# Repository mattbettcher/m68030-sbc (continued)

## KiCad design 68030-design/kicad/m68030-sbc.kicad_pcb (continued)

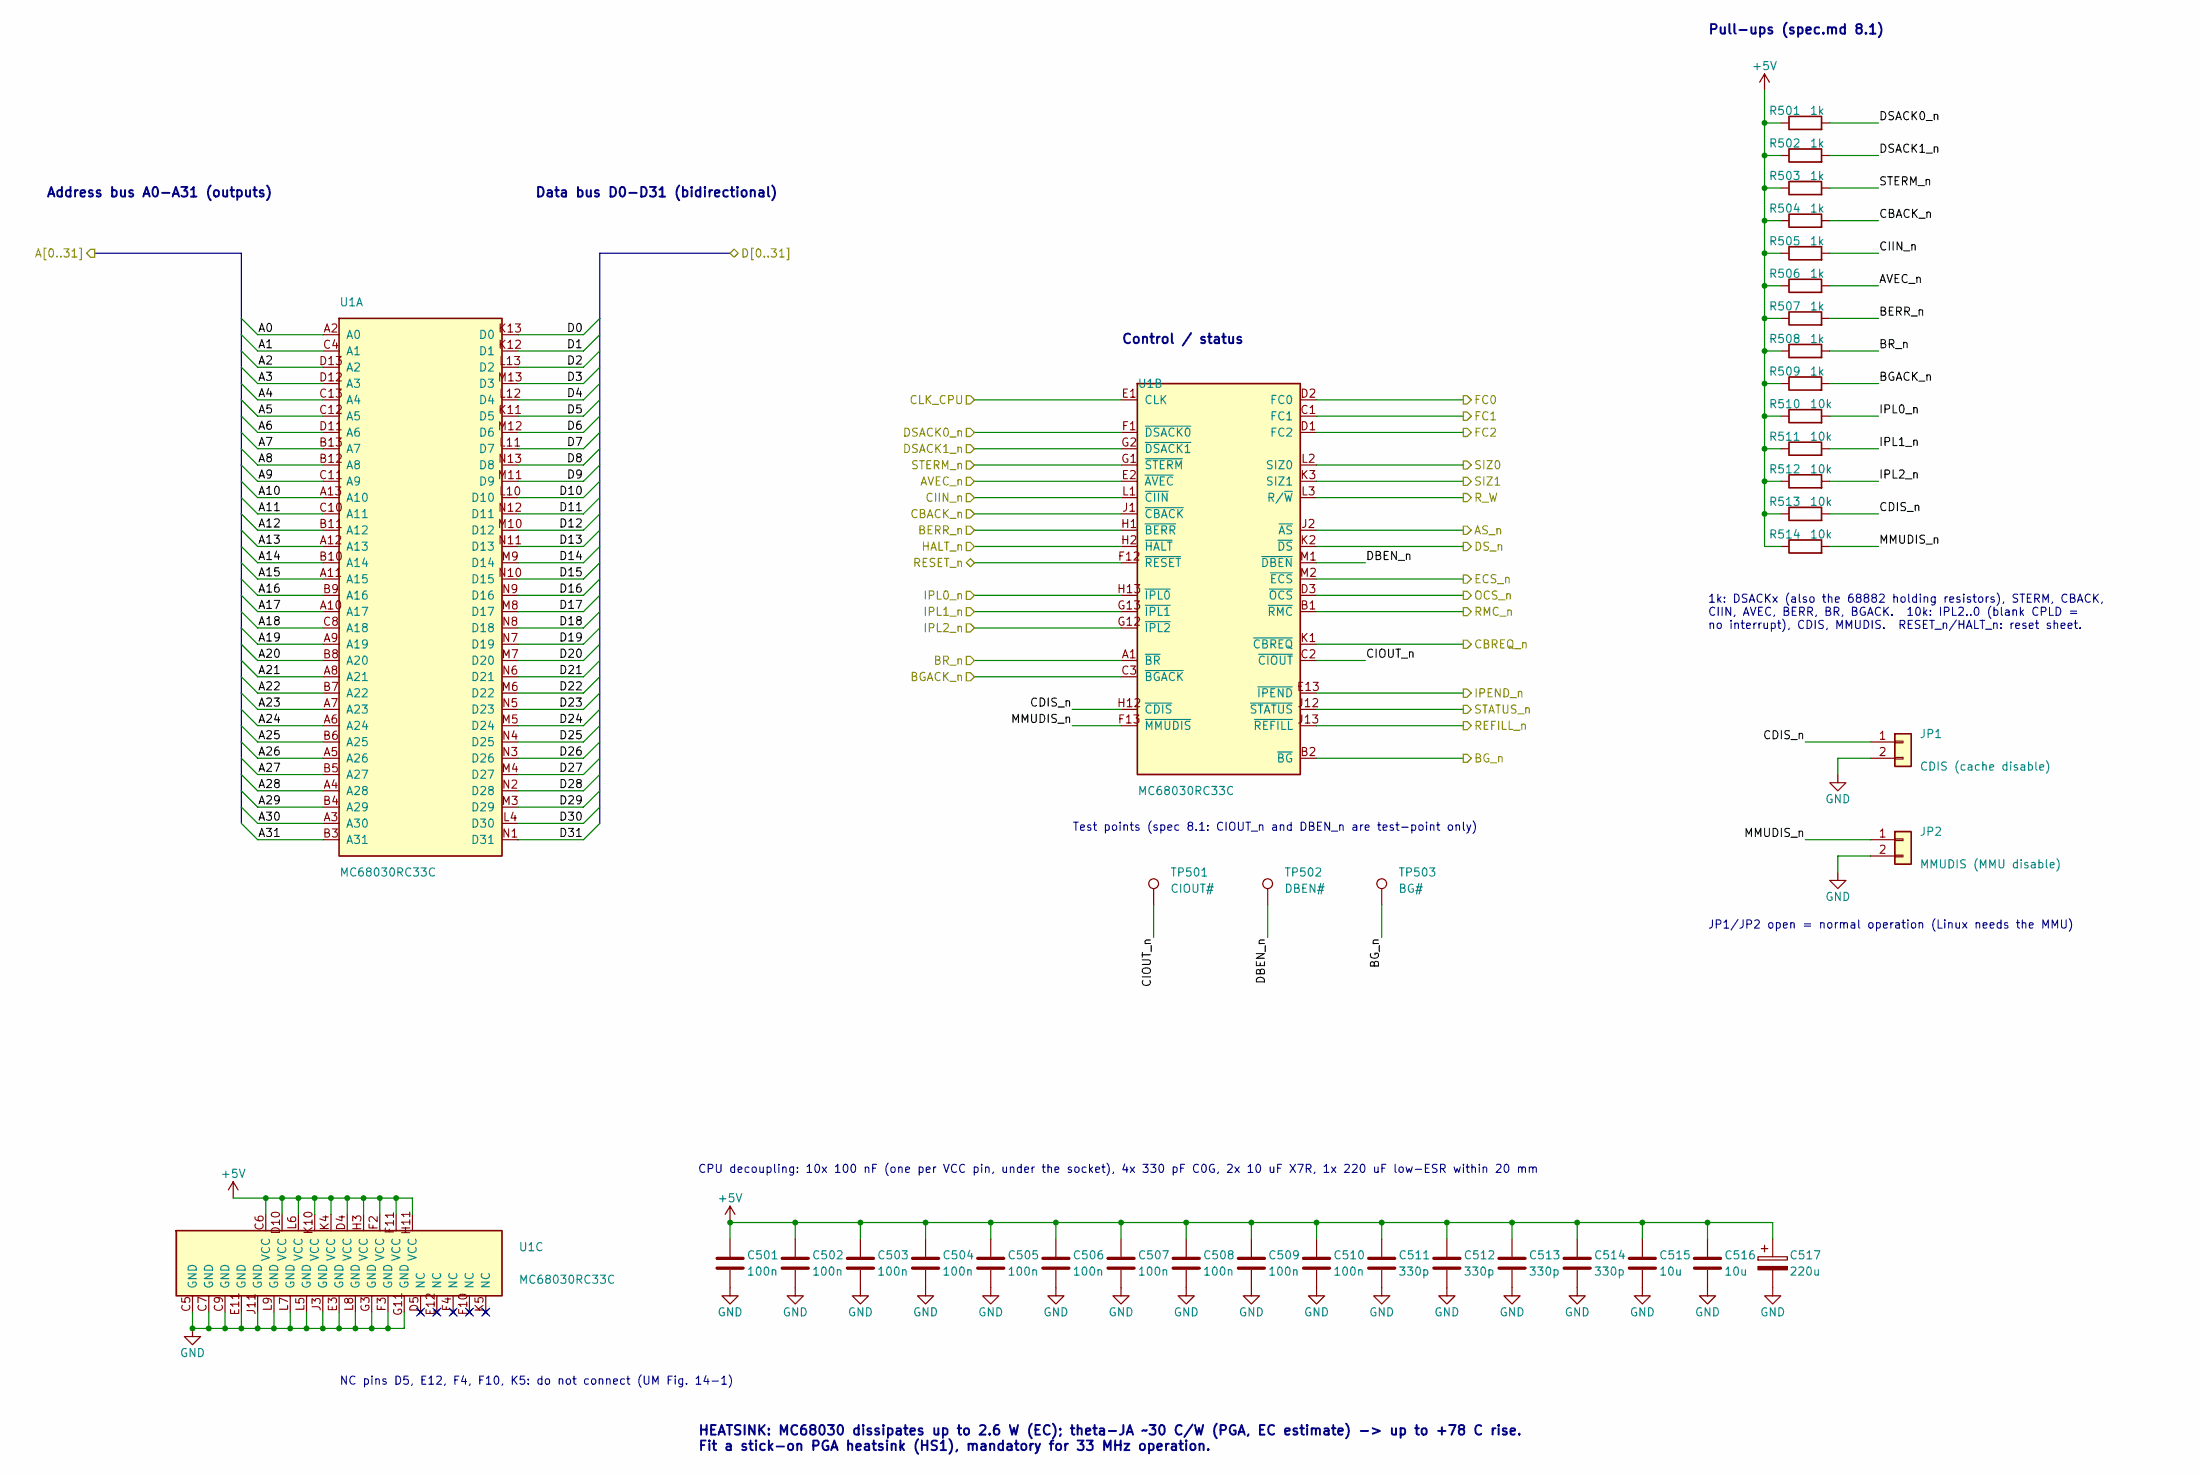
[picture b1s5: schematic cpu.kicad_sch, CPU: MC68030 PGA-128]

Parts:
C501, C502, C503, C504, C505, C506, C507, C508, C509, C510: 100n; C_0805_2012Metric
C511, C512, C513, C514: 330p; C_0603_1608Metric
C515, C516: 10u; C_1206_3216Metric
C517: 220u; CP_Radial_D8.0mm_P3.50mm
JP1: CDIS (cache disable); PinHeader_1x02_P2.54mm_Vertical
JP2: MMUDIS (MMU disable); PinHeader_1x02_P2.54mm_Vertical
R501, R502, R503, R504, R505, R506, R507, R508, R509: 1k; R_0603_1608Metric
R510, R511, R512, R513, R514: 10k; R_0603_1608Metric
TP501: CIOUT#; TestPoint_Pad_D1.5mm
TP502: DBEN#; TestPoint_Pad_D1.5mm
TP503: BG#; TestPoint_Pad_D1.5mm
U1: MC68030RC33C; PGA128_13x13_MC68030; MPN MC68030RC33C

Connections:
+5V: C501.1, C502.1, C503.1, C504.1, C505.1, C506.1, C507.1, C508.1, C509.1, C510.1, C511.1, C512.1, C513.1, C514.1, C515.1, C516.1, C517.1, R501.1, R502.1, R503.1, R504.1, R505.1, R506.1, R507.1, R508.1, R509.1, R510.1, R511.1, R512.1, R513.1, R514.1, U1.C6 (VCC), U1.D4 (VCC), U1.D10 (VCC), U1.F2 (VCC), U1.F11 (VCC), U1.H3 (VCC), U1.H11 (VCC), U1.K4 (VCC), U1.K10 (VCC), U1.L6 (VCC); also elsewhere on the board
/A0: U1.A2 (A0); also elsewhere on the board
/A1: U1.C4 (A1); also elsewhere on the board
/A2: U1.D13 (A2); also elsewhere on the board
/A3: U1.D12 (A3); also elsewhere on the board
/A4: U1.C13 (A4); also elsewhere on the board
/A5: U1.C12 (A5); also elsewhere on the board
/A6: U1.D11 (A6); also elsewhere on the board
/A7: U1.B13 (A7); also elsewhere on the board
/A8: U1.B12 (A8); also elsewhere on the board
/A9: U1.C11 (A9); also elsewhere on the board
/A10: U1.A13 (A10); also elsewhere on the board
/A11: U1.C10 (A11); also elsewhere on the board
/A12: U1.B11 (A12); also elsewhere on the board
/A13: U1.A12 (A13); also elsewhere on the board
/A14: U1.B10 (A14); also elsewhere on the board
/A15: U1.A11 (A15); also elsewhere on the board
/A16: U1.B9 (A16); also elsewhere on the board
/A17: U1.A10 (A17); also elsewhere on the board
/A18: U1.C8 (A18); also elsewhere on the board
/A19: U1.A9 (A19); also elsewhere on the board
/A20: U1.B8 (A20); also elsewhere on the board
/A21: U1.A8 (A21); also elsewhere on the board
/A22: U1.B7 (A22); also elsewhere on the board
/A23: U1.A7 (A23); also elsewhere on the board
/A24: U1.A6 (A24); also elsewhere on the board
/A25: U1.B6 (A25); also elsewhere on the board
/A26: U1.A5 (A26); also elsewhere on the board
/A27: U1.B5 (A27); also elsewhere on the board
/A28: U1.A4 (A28); also elsewhere on the board
/A29: U1.B4 (A29); also elsewhere on the board
/A30: U1.A3 (A30); also elsewhere on the board
/A31: U1.B3 (A31); also elsewhere on the board
/AS_n: U1.J2 (~AS); also elsewhere on the board
/AVEC_n: R506.2, U1.E2 (~AVEC); also elsewhere on the board
/BERR_n: R507.2, U1.H1 (~BERR); also elsewhere on the board
/BGACK_n: R509.2, U1.C3 (~BGACK); also elsewhere on the board
/BG_n: TP503.1, U1.B2 (~BG); also elsewhere on the board
/BR_n: R508.2, U1.A1 (~BR); also elsewhere on the board
/CBACK_n: R504.2, U1.J1 (~CBACK); also elsewhere on the board
/CBREQ_n: U1.K1 (~CBREQ); also elsewhere on the board
/CIIN_n: R505.2, U1.L1 (~CIIN); also elsewhere on the board
/CLK_CPU: U1.E1 (CLK); also elsewhere on the board
/D0: U1.K13 (D0); also elsewhere on the board
/D1: U1.K12 (D1); also elsewhere on the board
/D2: U1.L13 (D2); also elsewhere on the board
/D3: U1.M13 (D3); also elsewhere on the board
/D4: U1.L12 (D4); also elsewhere on the board
/D5: U1.K11 (D5); also elsewhere on the board
/D6: U1.M12 (D6); also elsewhere on the board
/D7: U1.L11 (D7); also elsewhere on the board
/D8: U1.N13 (D8); also elsewhere on the board
/D9: U1.M11 (D9); also elsewhere on the board
/D10: U1.L10 (D10); also elsewhere on the board
/D11: U1.N12 (D11); also elsewhere on the board
/D12: U1.M10 (D12); also elsewhere on the board
/D13: U1.N11 (D13); also elsewhere on the board
/D14: U1.M9 (D14); also elsewhere on the board
/D15: U1.N10 (D15); also elsewhere on the board
/D16: U1.N9 (D16); also elsewhere on the board
/D17: U1.M8 (D17); also elsewhere on the board
/D18: U1.N8 (D18); also elsewhere on the board
/D19: U1.N7 (D19); also elsewhere on the board
/D20: U1.M7 (D20); also elsewhere on the board
/D21: U1.N6 (D21); also elsewhere on the board
/D22: U1.M6 (D22); also elsewhere on the board
/D23: U1.N5 (D23); also elsewhere on the board
/D24: U1.M5 (D24); also elsewhere on the board
/D25: U1.N4 (D25); also elsewhere on the board
/D26: U1.N3 (D26); also elsewhere on the board
/D27: U1.M4 (D27); also elsewhere on the board
/D28: U1.N2 (D28); also elsewhere on the board
/D29: U1.M3 (D29); also elsewhere on the board
/D30: U1.L4 (D30); also elsewhere on the board
/D31: U1.N1 (D31); also elsewhere on the board
/DSACK0_n: R501.2, U1.F1 (~DSACK0); also elsewhere on the board
/DSACK1_n: R502.2, U1.G2 (~DSACK1); also elsewhere on the board
/DS_n: U1.K2 (~DS); also elsewhere on the board
/ECS_n: U1.M2 (~ECS); also elsewhere on the board
/FC0: U1.D2 (FC0); also elsewhere on the board
/FC1: U1.C1 (FC1); also elsewhere on the board
/FC2: U1.D1 (FC2); also elsewhere on the board
/HALT_n: U1.H2 (~HALT); also elsewhere on the board
/IPEND_n: U1.E13 (~IPEND); also elsewhere on the board
/IPL0_n: R510.2, U1.H13 (~IPL0); also elsewhere on the board
/IPL1_n: R511.2, U1.G13 (~IPL1); also elsewhere on the board
/IPL2_n: R512.2, U1.G12 (~IPL2); also elsewhere on the board
/OCS_n: U1.D3 (~OCS); also elsewhere on the board
/REFILL_n: U1.J13 (~REFILL); also elsewhere on the board
/RESET_n: U1.F12 (~RESET); also elsewhere on the board
/RMC_n: U1.B1 (~RMC); also elsewhere on the board
/R_W: U1.L3 (R/~W); also elsewhere on the board
/SIZ0: U1.L2 (SIZ0); also elsewhere on the board
/SIZ1: U1.K3 (SIZ1); also elsewhere on the board
/STATUS_n: U1.J12 (~STATUS); also elsewhere on the board
/STERM_n: R503.2, U1.G1 (~STERM); also elsewhere on the board
/cpu/CDIS_n: JP1.1, R513.2, U1.H12 (~CDIS)
/cpu/CIOUT_n: TP501.1, U1.C2 (~CIOUT)
/cpu/DBEN_n: TP502.1, U1.M1 (~DBEN)
/cpu/MMUDIS_n: JP2.1, R514.2, U1.F13 (~MMUDIS)
GND: C501.2, C502.2, C503.2, C504.2, C505.2, C506.2, C507.2, C508.2, C509.2, C510.2, C511.2, C512.2, C513.2, C514.2, C515.2, C516.2, C517.2, JP1.2, JP2.2, U1.C5 (GND), U1.C7 (GND), U1.C9 (GND), U1.E3 (GND), U1.E11 (GND), U1.F3 (GND), U1.G3 (GND), U1.G11 (GND), U1.J3 (GND), U1.J11 (GND), U1.L5 (GND), U1.L7 (GND), U1.L8 (GND), U1.L9 (GND); also elsewhere on the board

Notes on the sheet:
Address bus A0-A31 (outputs)
Data bus D0-D31 (bidirectional)
Control / status
Test points (spec 8.1: CIOUT_n and DBEN_n are test-point only)
Pull-ups (spec.md 8.1)
1k: DSACKx (also the 68882 holding resistors), STERM, CBACK, CIIN, AVEC, BERR, BR, BGACK. 10k: IPL2..0 (blank CPLD = no interrupt), CDIS, MMUDIS. RESET_n/HALT_n: reset sheet.
JP1/JP2 open = normal operation (Linux needs the MMU)
NC pins D5, E12, F4, F10, K5: do not connect (UM Fig. 14-1)
CPU decoupling: 10x 100 nF (one per VCC pin, under the socket), 4x 330 pF C0G, 2x 10 uF X7R, 1x 220 uF low-ESR within 20 mm
HEATSINK: MC68030 dissipates up to 2.6 W (EC); theta-JA ~30 C/W (PGA, EC estimate) -> up to +78 C rise. Fit a stick-on PGA heatsink (HS1), mandatory for 33 MHz operation.

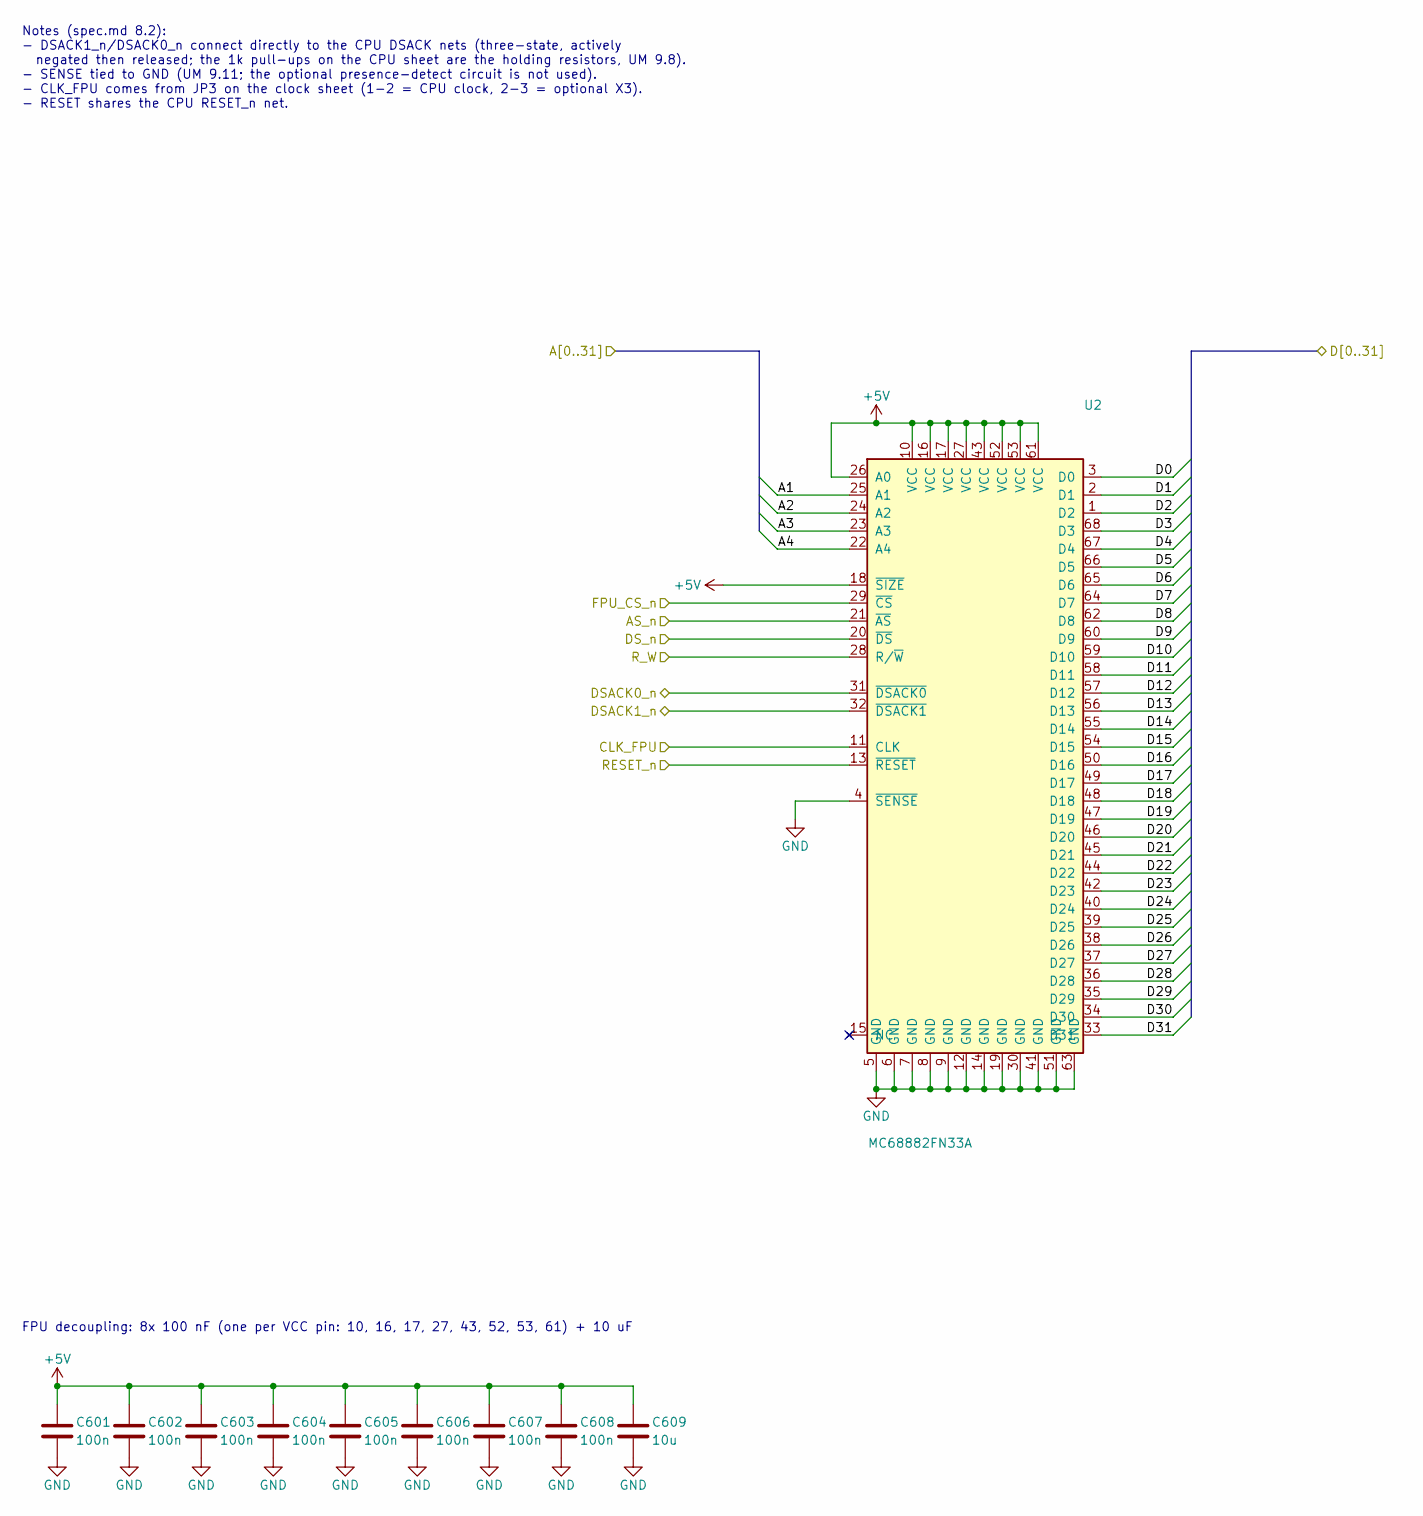
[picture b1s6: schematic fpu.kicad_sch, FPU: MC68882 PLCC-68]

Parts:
C601, C602, C603, C604, C605, C606, C607, C608: 100n; C_0805_2012Metric
C609: 10u; C_1206_3216Metric
U2: MC68882FN33A; PLCC-68_THT-Socket; MPN MC68882FN33A (or FN25A)

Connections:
+5V: C601.1, C602.1, C603.1, C604.1, C605.1, C606.1, C607.1, C608.1, C609.1, U2.10 (VCC), U2.16 (VCC), U2.17 (VCC), U2.18 (~SIZE), U2.26 (A0), U2.27 (VCC), U2.43 (VCC), U2.52 (VCC), U2.53 (VCC), U2.61 (VCC); also elsewhere on the board
/A1: U2.25 (A1); also elsewhere on the board
/A2: U2.24 (A2); also elsewhere on the board
/A3: U2.23 (A3); also elsewhere on the board
/A4: U2.22 (A4); also elsewhere on the board
/AS_n: U2.21 (~AS); also elsewhere on the board
/CLK_FPU: U2.11 (CLK); also elsewhere on the board
/D0: U2.3 (D0); also elsewhere on the board
/D1: U2.2 (D1); also elsewhere on the board
/D2: U2.1 (D2); also elsewhere on the board
/D3: U2.68 (D3); also elsewhere on the board
/D4: U2.67 (D4); also elsewhere on the board
/D5: U2.66 (D5); also elsewhere on the board
/D6: U2.65 (D6); also elsewhere on the board
/D7: U2.64 (D7); also elsewhere on the board
/D8: U2.62 (D8); also elsewhere on the board
/D9: U2.60 (D9); also elsewhere on the board
/D10: U2.59 (D10); also elsewhere on the board
/D11: U2.58 (D11); also elsewhere on the board
/D12: U2.57 (D12); also elsewhere on the board
/D13: U2.56 (D13); also elsewhere on the board
/D14: U2.55 (D14); also elsewhere on the board
/D15: U2.54 (D15); also elsewhere on the board
/D16: U2.50 (D16); also elsewhere on the board
/D17: U2.49 (D17); also elsewhere on the board
/D18: U2.48 (D18); also elsewhere on the board
/D19: U2.47 (D19); also elsewhere on the board
/D20: U2.46 (D20); also elsewhere on the board
/D21: U2.45 (D21); also elsewhere on the board
/D22: U2.44 (D22); also elsewhere on the board
/D23: U2.42 (D23); also elsewhere on the board
/D24: U2.40 (D24); also elsewhere on the board
/D25: U2.39 (D25); also elsewhere on the board
/D26: U2.38 (D26); also elsewhere on the board
/D27: U2.37 (D27); also elsewhere on the board
/D28: U2.36 (D28); also elsewhere on the board
/D29: U2.35 (D29); also elsewhere on the board
/D30: U2.34 (D30); also elsewhere on the board
/D31: U2.33 (D31); also elsewhere on the board
/DSACK0_n: U2.31 (~DSACK0); also elsewhere on the board
/DSACK1_n: U2.32 (~DSACK1); also elsewhere on the board
/DS_n: U2.20 (~DS); also elsewhere on the board
/FPU_CS_n: U2.29 (~CS); also elsewhere on the board
/RESET_n: U2.13 (~RESET); also elsewhere on the board
/R_W: U2.28 (R/~W); also elsewhere on the board
GND: C601.2, C602.2, C603.2, C604.2, C605.2, C606.2, C607.2, C608.2, C609.2, U2.4 (~SENSE), U2.5 (GND), U2.6 (GND), U2.7 (GND), U2.8 (GND), U2.9 (GND), U2.12 (GND), U2.14 (GND), U2.19 (GND), U2.30 (GND), U2.41 (GND), U2.51 (GND), U2.63 (GND); also elsewhere on the board

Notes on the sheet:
FPU decoupling: 8x 100 nF (one per VCC pin: 10, 16, 17, 27, 43, 52, 53, 61) + 10 uF
Notes (spec.md 8.2): - DSACK1_n/DSACK0_n connect directly to the CPU DSACK nets (three-state, actively negated then released; the 1k pull-ups on the CPU sheet are the holding resistors, UM 9.8). - SENSE tied to GND (UM 9.11; the optional presence-detect circuit is not used). - CLK_FPU comes from JP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

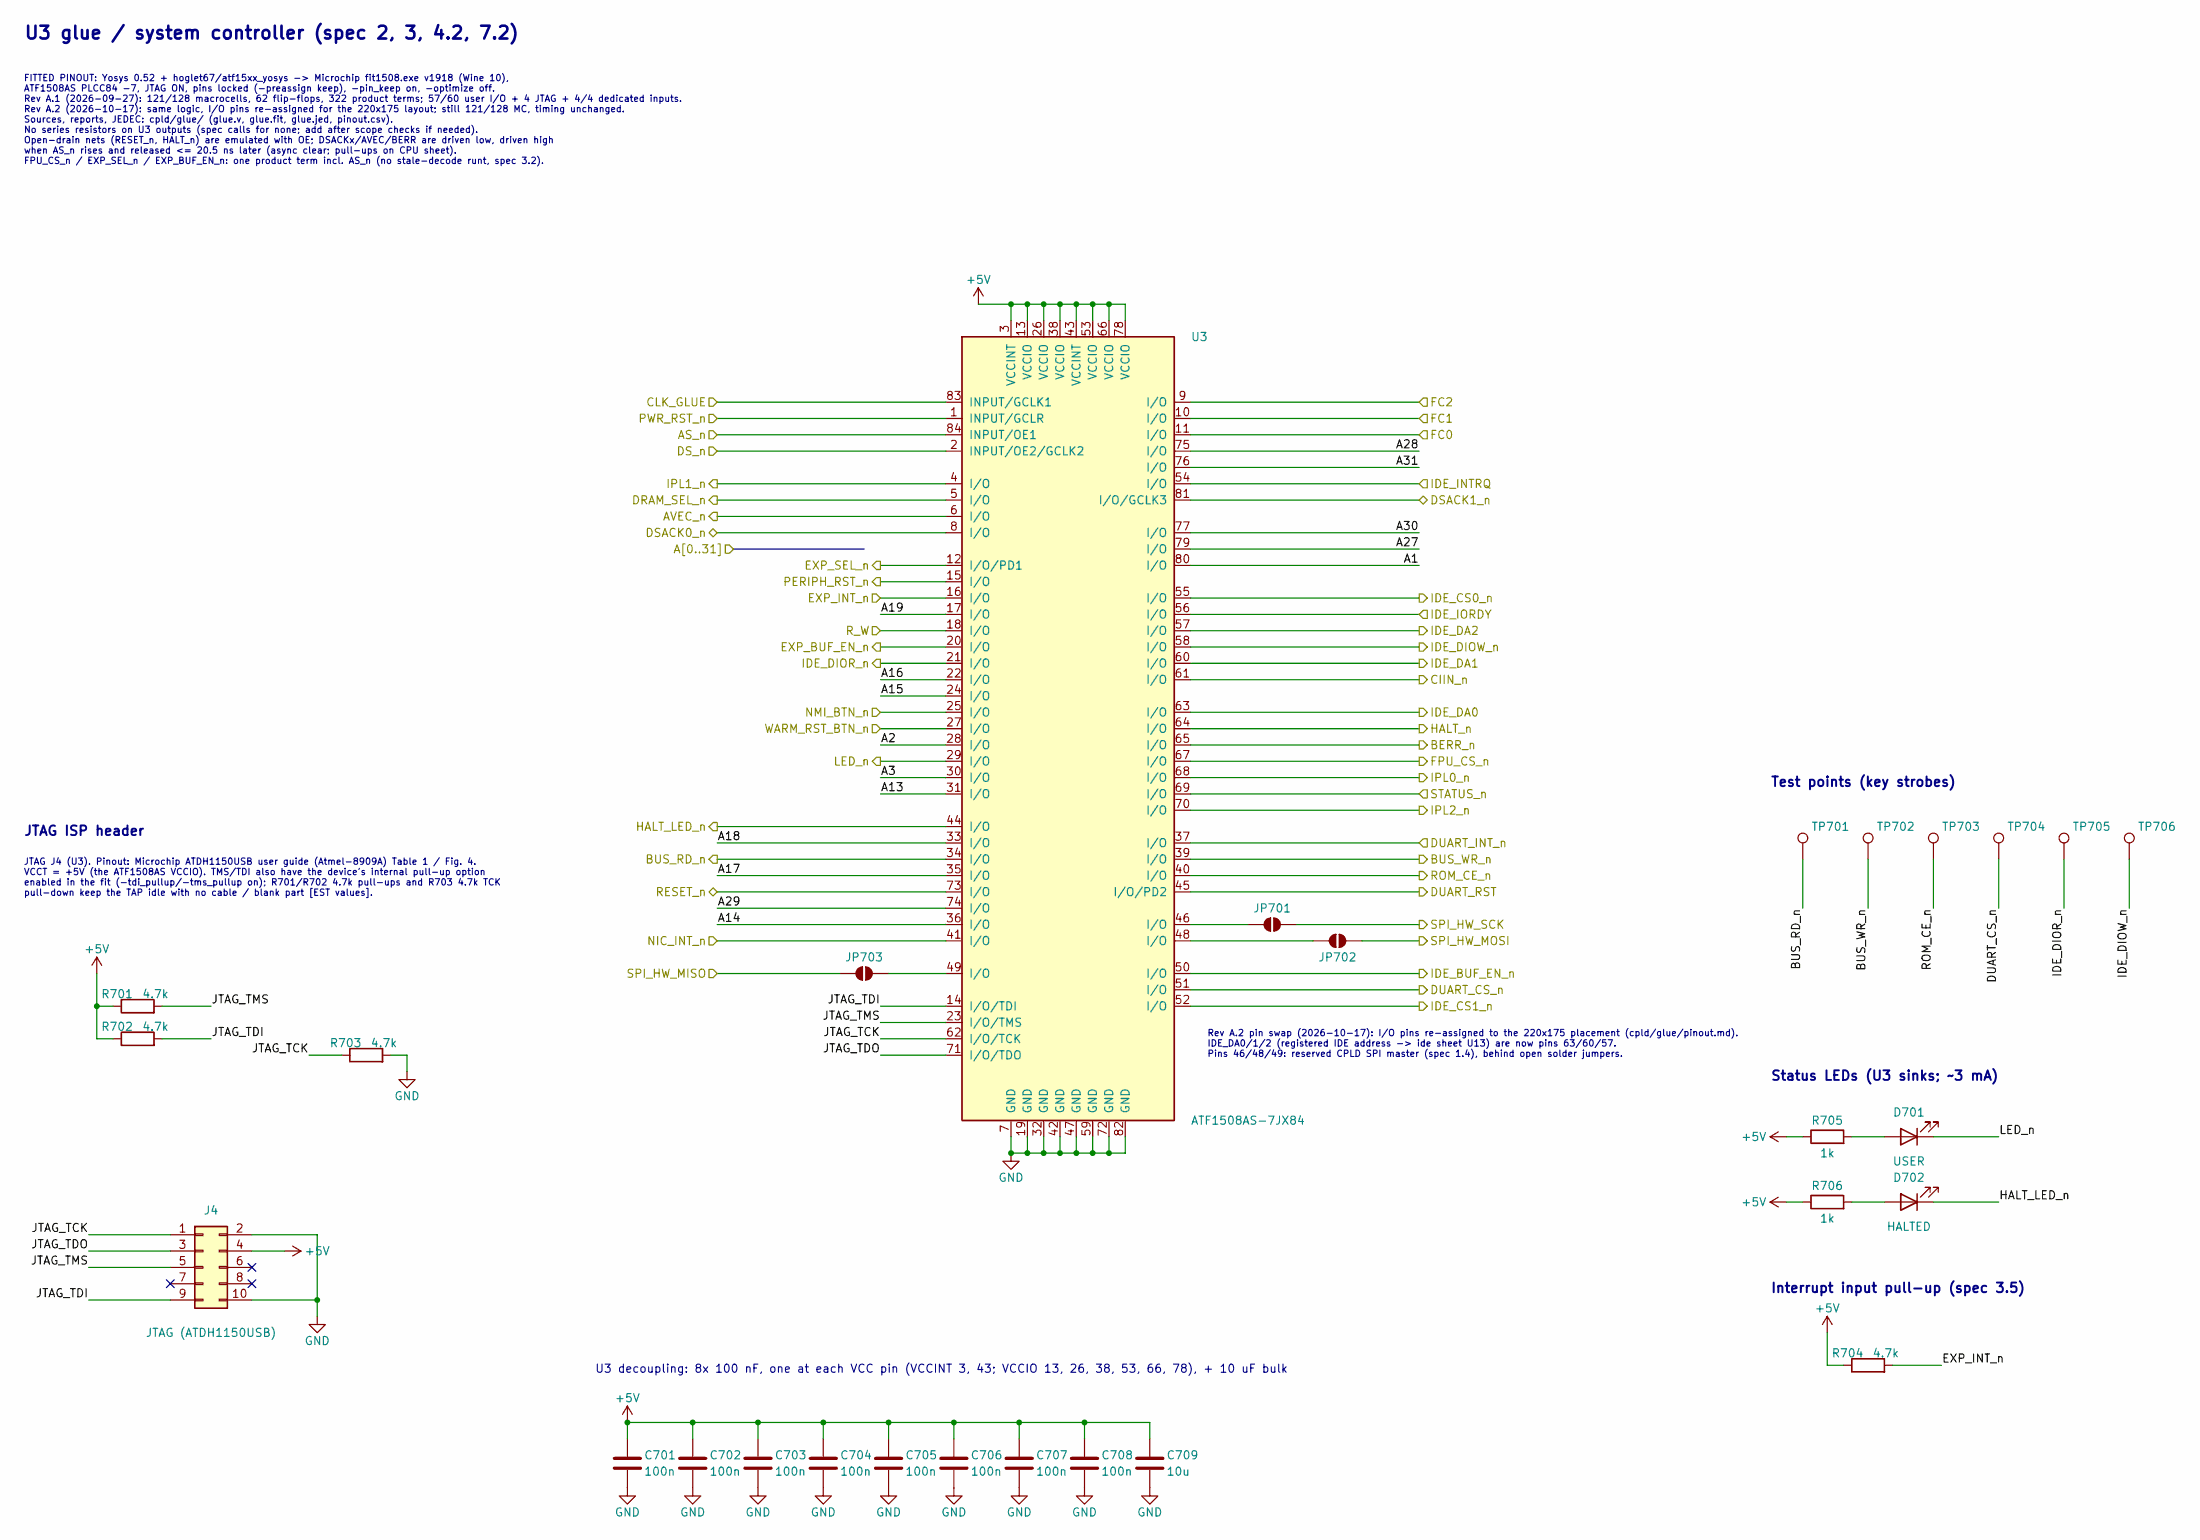
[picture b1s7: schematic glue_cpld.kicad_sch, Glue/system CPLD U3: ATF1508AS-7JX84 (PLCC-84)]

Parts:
C701, C702, C703, C704, C705, C706, C707, C708: 100n; C_0805_2012Metric
C709: 10u; C_1206_3216Metric
D701: USER; LED_0805_2012Metric
D702: HALTED; LED_0805_2012Metric
J4: JTAG (ATDH1150USB); IDC-Header_2x05_P2.54mm_Vertical
JP701, JP702, JP703: open; SolderJumper-2_P1.3mm_Open_RoundedPad1.0x1.5mm
R701, R702, R703, R704: 4.7k; R_0603_1608Metric
R705, R706: 1k; R_0603_1608Metric
TP701: BUS_RD#; TestPoint_Pad_D1.5mm
TP702: BUS_WR#; TestPoint_Pad_D1.5mm
TP703: ROM_CE#; TestPoint_Pad_D1.5mm
TP704: DUART_CS#; TestPoint_Pad_D1.5mm
TP705: IDE_DIOR#; TestPoint_Pad_D1.5mm
TP706: IDE_DIOW#; TestPoint_Pad_D1.5mm
U3: ATF1508AS-7JX84; PLCC-84_THT-Socket; MPN ATF1508AS-7JX84

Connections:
+5V: C701.1, C702.1, C703.1, C704.1, C705.1, C706.1, C707.1, C708.1, C709.1, J4.4, R701.1, R702.1, R704.1, R705.1, R706.1, U3.3 (VCCINT), U3.13 (VCCIO), U3.26 (VCCIO), U3.38 (VCCIO), U3.43 (VCCINT), U3.53 (VCCIO), U3.66 (VCCIO), U3.78 (VCCIO); also elsewhere on the board
/A1: U3.80 (I/O); also elsewhere on the board
/A2: U3.28 (I/O); also elsewhere on the board
/A3: U3.30 (I/O); also elsewhere on the board
/A13: U3.31 (I/O); also elsewhere on the board
/A14: U3.36 (I/O); also elsewhere on the board
/A15: U3.24 (I/O); also elsewhere on the board
/A16: U3.22 (I/O); also elsewhere on the board
/A17: U3.35 (I/O); also elsewhere on the board
/A18: U3.33 (I/O); also elsewhere on the board
/A19: U3.17 (I/O); also elsewhere on the board
/A27: U3.79 (I/O); also elsewhere on the board
/A28: U3.75 (I/O); also elsewhere on the board
/A29: U3.74 (I/O); also elsewhere on the board
/A30: U3.77 (I/O); also elsewhere on the board
/A31: U3.76 (I/O); also elsewhere on the board
/AS_n: U3.84 (INPUT/OE1); also elsewhere on the board
/AVEC_n: U3.6 (I/O); also elsewhere on the board
/BERR_n: U3.65 (I/O); also elsewhere on the board
/BUS_RD_n: TP701.1, U3.34 (I/O); also elsewhere on the board
/BUS_WR_n: TP702.1, U3.39 (I/O); also elsewhere on the board
/CIIN_n: U3.61 (I/O); also elsewhere on the board
/CLK_GLUE: U3.83 (INPUT/GCLK1); also elsewhere on the board
/DRAM_SEL_n: U3.5 (I/O); also elsewhere on the board
/DSACK0_n: U3.8 (I/O); also elsewhere on the board
/DSACK1_n: U3.81 (I/O/GCLK3); also elsewhere on the board
/DS_n: U3.2 (INPUT/OE2/GCLK2); also elsewhere on the board
/DUART_CS_n: TP704.1, U3.51 (I/O); also elsewhere on the board
/DUART_INT_n: U3.37 (I/O); also elsewhere on the board
/DUART_RST: U3.45 (I/O/PD2); also elsewhere on the board
/EXP_BUF_EN_n: U3.20 (I/O); also elsewhere on the board
/EXP_INT_n: R704.2, U3.16 (I/O); also elsewhere on the board
/EXP_SEL_n: U3.12 (I/O/PD1); also elsewhere on the board
/FC0: U3.11 (I/O); also elsewhere on the board
/FC1: U3.10 (I/O); also elsewhere on the board
/FC2: U3.9 (I/O); also elsewhere on the board
/FPU_CS_n: U3.67 (I/O); also elsewhere on the board
/HALT_LED_n: D702.1 (K), U3.44 (I/O); also elsewhere on the board
/HALT_n: U3.64 (I/O); also elsewhere on the board
/IDE_BUF_EN_n: U3.50 (I/O); also elsewhere on the board
/IDE_CS0_n: U3.55 (I/O); also elsewhere on the board
/IDE_CS1_n: U3.52 (I/O); also elsewhere on the board
/IDE_DA0: U3.63 (I/O); also elsewhere on the board
/IDE_DA1: U3.60 (I/O); also elsewhere on the board
/IDE_DA2: U3.57 (I/O); also elsewhere on the board
/IDE_DIOR_n: TP705.1, U3.21 (I/O); also elsewhere on the board
/IDE_DIOW_n: TP706.1, U3.58 (I/O); also elsewhere on the board
/IDE_INTRQ: U3.54 (I/O); also elsewhere on the board
/IDE_IORDY: U3.56 (I/O); also elsewhere on the board
/IPL0_n: U3.68 (I/O); also elsewhere on the board
/IPL1_n: U3.4 (I/O); also elsewhere on the board
/IPL2_n: U3.70 (I/O); also elsewhere on the board
/LED_n: D701.1 (K), U3.29 (I/O); also elsewhere on the board
/NIC_INT_n: U3.41 (I/O); also elsewhere on the board
/NMI_BTN_n: U3.25 (I/O); also elsewhere on the board
/PERIPH_RST_n: U3.15 (I/O); also elsewhere on the board
/PWR_RST_n: U3.1 (INPUT/GCLR); also elsewhere on the board
/RESET_n: U3.73 (I/O); also elsewhere on the board
/ROM_CE_n: TP703.1, U3.40 (I/O); also elsewhere on the board
/R_W: U3.18 (I/O); also elsewhere on the board
/SPI_HW_MISO: JP703.1 (A); also elsewhere on the board
/SPI_HW_MOSI: JP702.2 (B); also elsewhere on the board
/SPI_HW_SCK: JP701.2 (B); also elsewhere on the board
/STATUS_n: U3.69 (I/O); also elsewhere on the board
/WARM_RST_BTN_n: U3.27 (I/O); also elsewhere on the board
/glue_cpld/JTAG_TCK: J4.1, R703.1, U3.62 (I/O/TCK)
/glue_cpld/JTAG_TDI: J4.9, R702.2, U3.14 (I/O/TDI)
/glue_cpld/JTAG_TDO: J4.3, U3.71 (I/O/TDO)
/glue_cpld/JTAG_TMS: J4.5, R701.2, U3.23 (I/O/TMS)
GND: C701.2, C702.2, C703.2, C704.2, C705.2, C706.2, C707.2, C708.2, C709.2, J4.2, J4.10, R703.2, U3.7 (GND), U3.19 (GND), U3.32 (GND), U3.42 (GND), U3.47 (GND), U3.59 (GND), U3.72 (GND), U3.82 (GND); also elsewhere on the board
unnamed: D701.2 (A), R705.2
unnamed: D702.2 (A), R706.2
unnamed: JP701.1 (A), U3.46 (I/O)
unnamed: JP702.1 (A), U3.48 (I/O)
unnamed: JP703.2 (B), U3.49 (I/O)

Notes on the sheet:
Rev A.2 pin swap (2026-10-17): I/O pins re-assigned to the 220x175 placement (cpld/glue/pinout.md). IDE_DA0/1/2 (registered IDE address -> ide sheet U13) are now pins 63/60/57. Pins 46/48/49: reserved CPLD SPI master (spec 1.4), behind open solder jumpers.
U3 decoupling: 8x 100 nF, one at each VCC pin (VCCINT 3, 43; VCCIO 13, 26, 38, 53, 66, 78), + 10 uF bulk
JTAG J4 (U3). Pinout: Microchip ATDH1150USB user guide (Atmel-8909A) Table 1 / Fig. 4. VCCT = +5V (the ATF1508AS VCCIO). TMS/TDI also have the device's internal pull-up option enabled in the fit (-tdi_pullup/-tms_pullup on); R701/R702 4.7k pull-ups and R703 4.7k TCK pull-down keep the TAP idle with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
JTAG ISP header
Status LEDs (U3 sinks; ~3 mA)
Interrupt input pull-up (spec 3.5)
Test points (key strobes)
U3 glue / system controller (spec 2, 3, 4.2, 7.2)
FITTED PINOUT: Yosys 0.52 + hoglet67/atf15xx_yosys -> Microchip fit1508.exe v1918 (Wine 10), ATF1508AS PLCC84 -7, JTAG ON, pins locked (-preassign keep), -pin_keep on, -optimize off. Rev A.1 (2026-09-27): 121/128 macrocells, 62 flip-flops, 322 product terms; 57/60 user I/O + 4 JTAG + 4/4 dedicated 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
